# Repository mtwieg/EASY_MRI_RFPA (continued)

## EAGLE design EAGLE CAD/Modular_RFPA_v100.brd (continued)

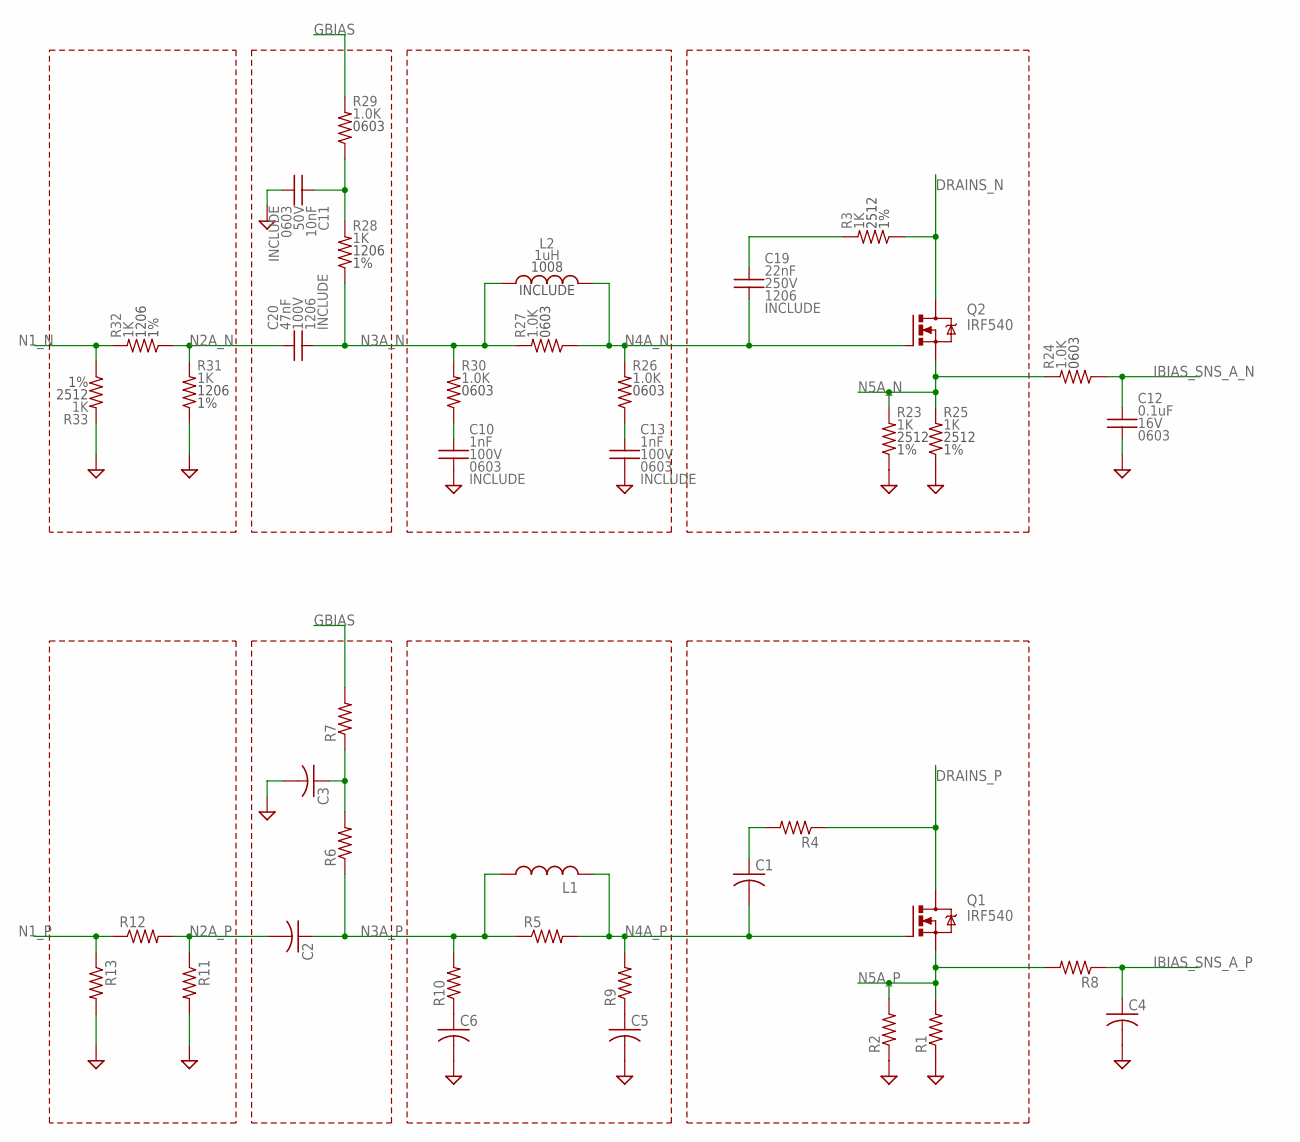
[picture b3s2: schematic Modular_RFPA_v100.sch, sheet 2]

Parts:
C1: C-USC1812; C1812
C2: C-USC0805; C0805
C3, C4, C5, C6: C-USC0603; C0603
C10, C13: 1nF; 0603_IPC-7351B
C11: 10nF; 0603_IPC-7351B
C12: 0.1uF; 0603_IPC-7351B
C19: 22nF; C1206
C20: 47nF; C1206
L1: L-USL1812; L1812
L2: 1uH; L1008
Q1, Q2: IRF540; TO220BV
R1, R2, R4, R11, R12, R13: R-US_R2512; R2512
R3, R23, R25, R33: 1K; R2512
R5, R6, R9, R10: R-US_R0805; R0805
R7, R8: R-US_R0603; R0603
R24, R26, R27, R29, R30: 1.0K; 0603_IPC-7351B
R28, R31, R32: 1K; R1206

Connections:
DRAINS_N: Q2.D, R3.2
DRAINS_P: Q1.D, R4.1
GBIAS: R7.2, R29.1; also elsewhere on the board
GND: C3.2, C4.2, C5.2, C6.2, C10.2, C11.2, C12.2, C13.2, R1.1, R2.1, R11.2, R13.2, R23.2, R25.2, R31.2, R33.1; also elsewhere on the board
IBIAS_SNS_A_N: C12.1, R24.2
IBIAS_SNS_A_P: C4.1, R8.1
N1_N: R32.1, R33.2
N1_P: R12.1, R13.1
N2A_N: C20.1, R31.1, R32.2
N2A_P: C2.2, R11.1, R12.2
N3A_N: C20.2, L2.1, R27.1, R28.2, R30.1
N3A_P: C2.1, L1.1, R5.1, R6.1, R10.2
N4A_N: C19.2, L2.2, Q2.G, R26.1, R27.2
N4A_P: C1.2, L1.2, Q1.G, R5.2, R9.2
N5A_N: Q2.S, R23.1, R24.1, R25.1
N5A_P: Q1.S, R1.2, R2.2, R8.2
unnamed: C1.1, R4.2
unnamed: C10.1, R30.2
unnamed: C3.1, R6.2, R7.1
unnamed: C19.1, R3.1
unnamed: C5.1, R9.1
unnamed: C6.1, R10.1
unnamed: C11.1, R28.1, R29.2
unnamed: C13.1, R26.2

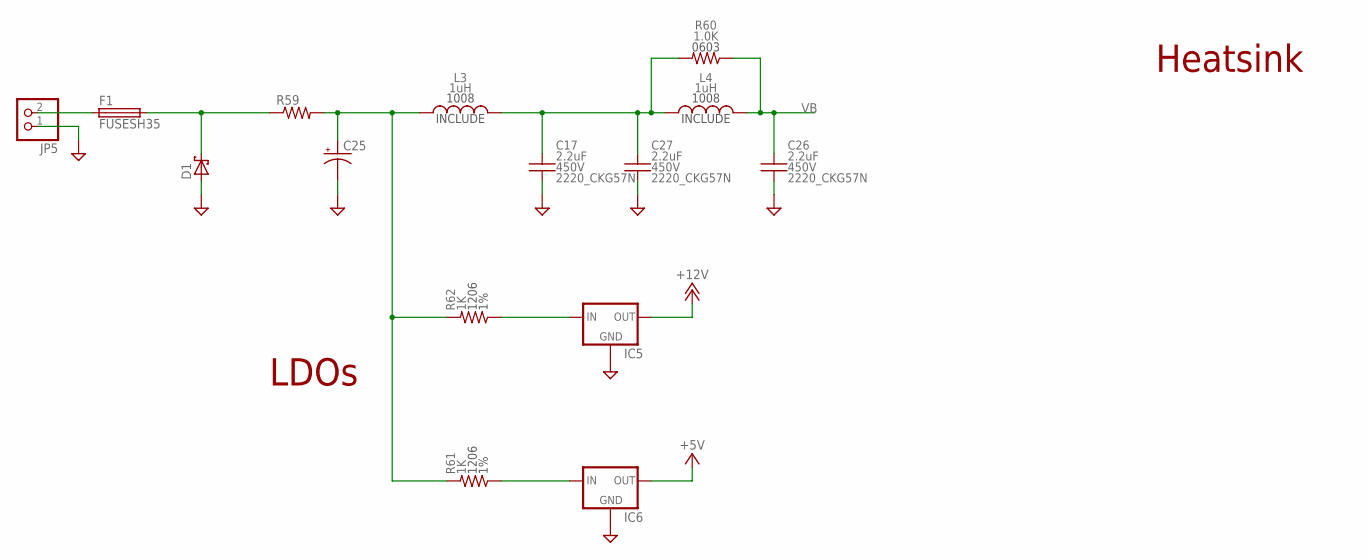
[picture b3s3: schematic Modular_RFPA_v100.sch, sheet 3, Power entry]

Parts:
C17, C26, C27: 2.2uF; C2220_CKG57N
C25: CPOL-USE10-25; EB25D
D1: SCHOTTKY-DIODESMC; SMC
F1: FUSESH35; SH25
IC5, IC6: 78XXS
JP5: PINHD-1X2; 1X02
L3, L4: 1uH; L1008
R59: R-US_0617/22; 0617/22
R60: 1.0K; 0603_IPC-7351B
R61, R62: 1K; R1206

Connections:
+5V: IC6.OUT
+12V: IC5.OUT; also elsewhere on the board
GND: C17.2, C25.-, C26.2, C27.2, D1.A, IC5.GND, IC6.GND, JP5.1; also elsewhere on the board
unnamed: IC5.IN, R62.2
unnamed: D1.C, F1.2, R59.1
unnamed: F1.1, JP5.2
unnamed: C25.+, L3.1, R59.2, R61.1, R62.1
unnamed: C17.1, C27.1, L3.2, L4.1, R60.1
unnamed: IC6.IN, R61.2
VB: C26.1, L4.2, R60.2

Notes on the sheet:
LDOs
Heatsink

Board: 4 copper layers, 100 parts (0 on the bottom side), 60 nets, no tracks yet.

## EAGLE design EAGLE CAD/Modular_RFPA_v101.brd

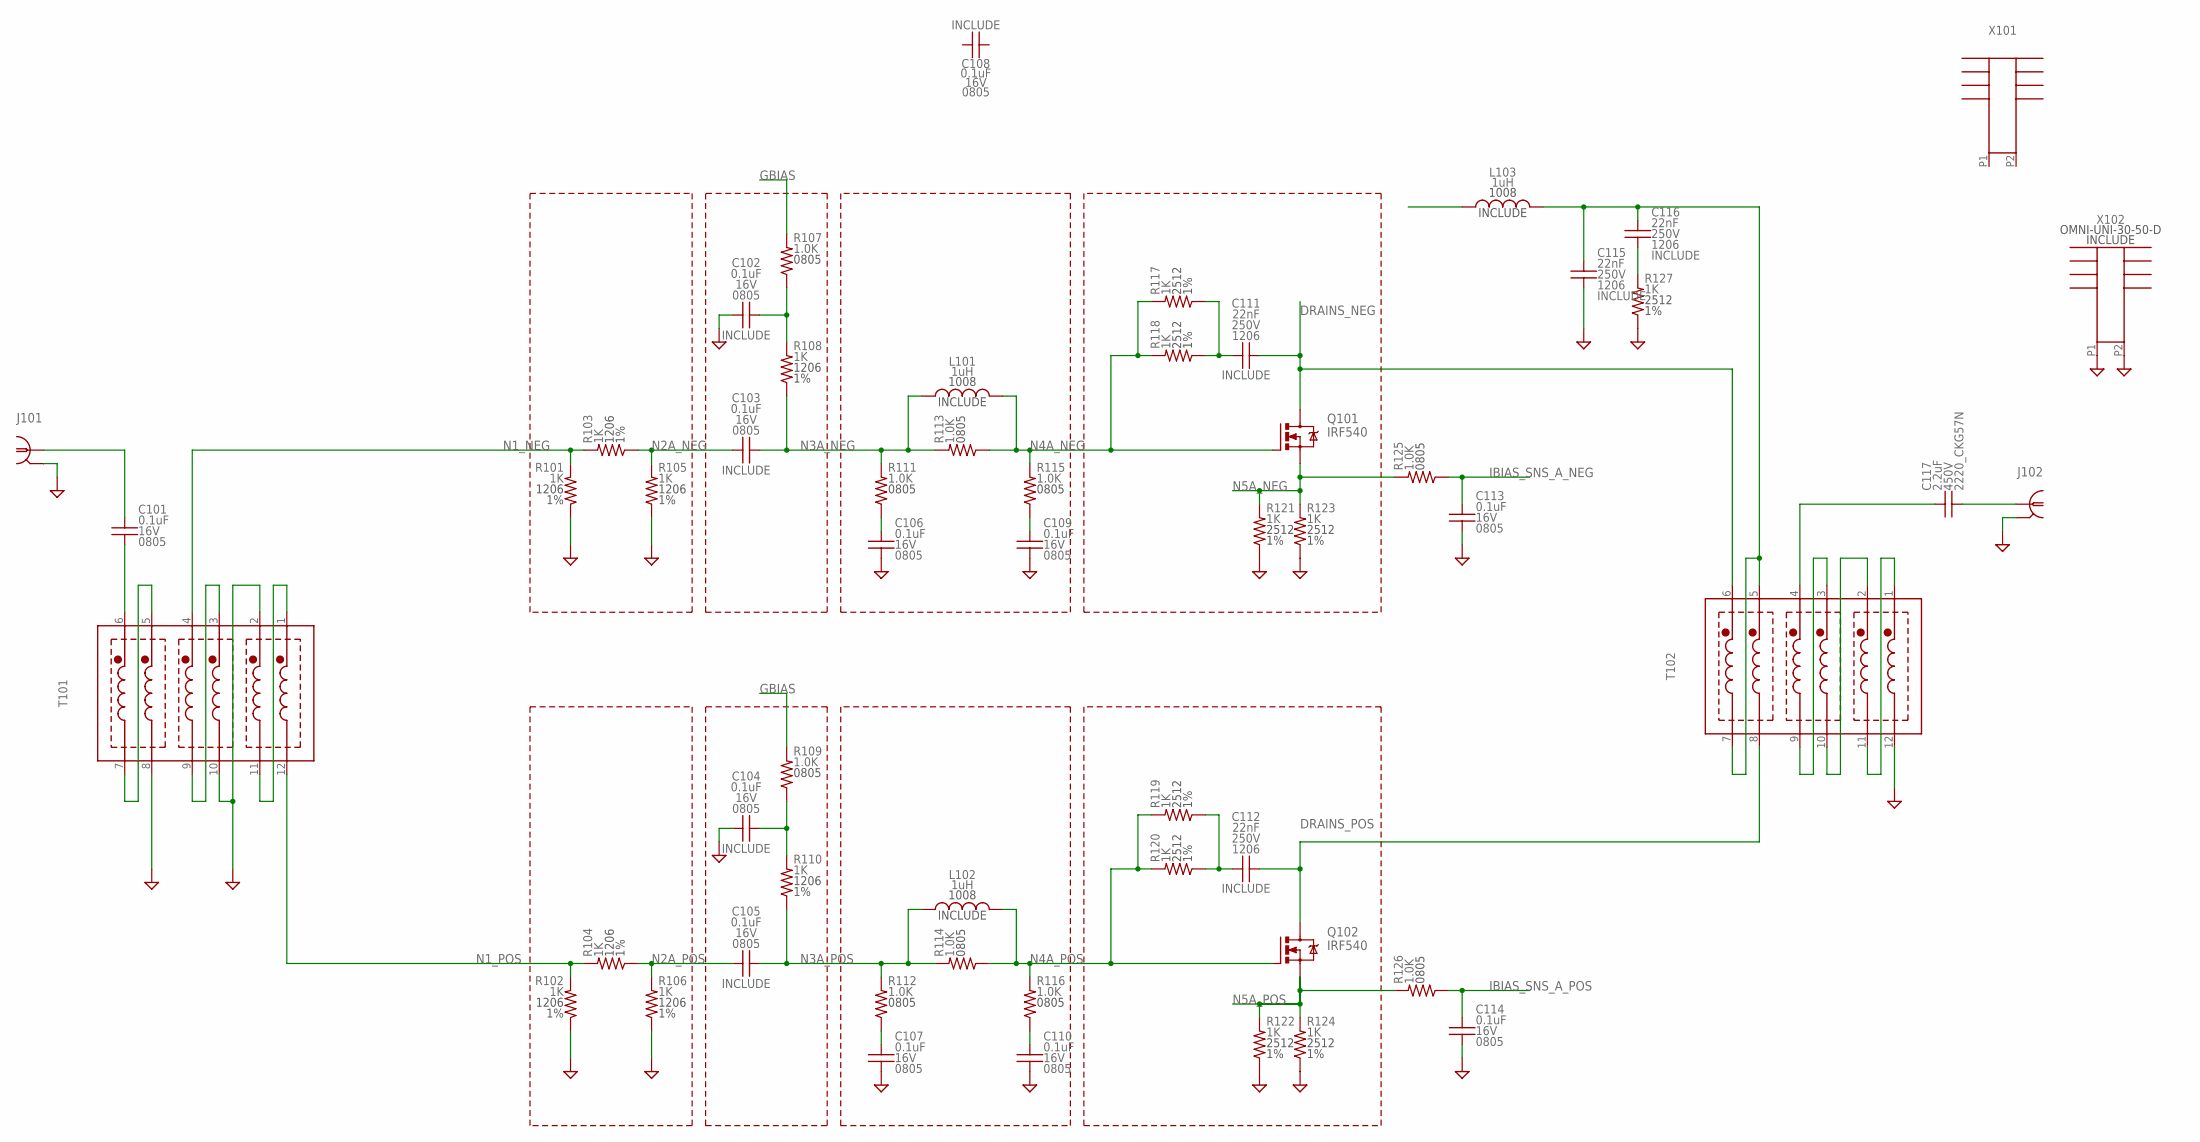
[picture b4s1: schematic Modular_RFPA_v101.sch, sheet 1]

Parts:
C101, C102, C103, C104, C105, C106, C107, C108, C109, C110, C113, C114: 0.1uF; 0805_IPC-7351B
C111, C112, C115, C116: 22nF; C1206
C117: 2.2uF; C2220_CKG57N
J101, J102: COAXBNC_EDGE; BNC_EDGE
L101, L102, L103: 1uH; L1008
Q101, Q102: IRF540; TO220BV
R101, R102, R103, R104, R105, R106, R108, R110: 1K; R1206
R107, R109, R111, R112, R113, R114, R115, R116, R125, R126: 1.0K; 0805_IPC-7351B
R117, R118, R119, R120, R121, R122, R123, R124, R127: 1K; R2512
T101, T102: HP5_TRAFOHP5; HP5
X101: HEATSINK_OMNI_DUAL30-75-D; OMNI-UNI-30-75-D
X102: HEATSINK_OMNI_DUALOMNI-UNI-30-50-DUNI-30-50-D; OMNI-UNI-30-50-D

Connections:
DRAINS_NEG: C111.2, Q101.D, T102.6 (S6)
DRAINS_POS: C112.2, Q102.D, T102.8 (F5)
GBIAS: R107.1, R109.1; also elsewhere on the board
GND: C102.2, C104.2, C106.2, C107.2, C109.2, C110.2, C113.2, C114.2, C115.2, J101.G1 (GND1), J101.G2 (GND1), J101.G3 (GND1), J101.G4 (GND1), J102.G1 (GND1), J102.G2 (GND1), J102.G3 (GND1), J102.G4 (GND1), R101.2, R102.2, R105.2, R106.2, R121.2, R122.2, R123.2, R124.2, R127.2, T101.2 (S2), T101.8 (F5), T101.10 (F3), T102.12 (F1), X102.P1, X102.P2; also elsewhere on the board
IBIAS_SNS_A_NEG: C113.1, R125.2
IBIAS_SNS_A_POS: C114.1, R126.2
N1_NEG: R101.1, R103.1, T101.4 (S4)
N1_POS: R102.1, R104.1, T101.12 (F1)
N2A_NEG: C103.2, R103.2, R105.1
N2A_POS: C105.2, R104.2, R106.1
N3A_NEG: C103.1, L101.1, R108.2, R111.1, R113.1
N3A_POS: C105.1, L102.1, R110.2, R112.1, R114.1
N4A_NEG: L101.2, Q101.G, R113.2, R115.1, R117.1, R118.1
N4A_POS: L102.2, Q102.G, R114.2, R116.1, R119.1, R120.1
N5A_NEG: Q101.S, R121.1, R123.1, R125.1
N5A_POS: Q102.S, R122.1, R124.1, R126.1
unnamed: C111.1, R117.2, R118.2
unnamed: C106.1, R111.2
unnamed: C104.1, R109.2, R110.1
unnamed: C107.1, R112.2
unnamed: C110.1, R116.2
unnamed: C112.1, R119.2, R120.2
unnamed: C102.1, R107.2, R108.1
unnamed: C109.1, R115.2
unnamed: T102.3 (S3), T102.9 (F4)
unnamed: T102.2 (S2), T102.10 (F3)
unnamed: T102.1 (S1), T102.11 (F2)
unnamed: T101.3 (S3), T101.9 (F4)
unnamed: C117.2, J102.C (1)
unnamed: C117.1, T102.4 (S4)
unnamed: T101.1 (S1), T101.11 (F2)
unnamed: C101.1, J101.C (1)
unnamed: C116.2, R127.1
unnamed: C101.2, T101.6 (S6)
VB_CT: C115.1, C116.1, L103.2, T102.5 (S5), T102.7 (F6)
VB_CT1: T101.5 (S5), T101.7 (F6)

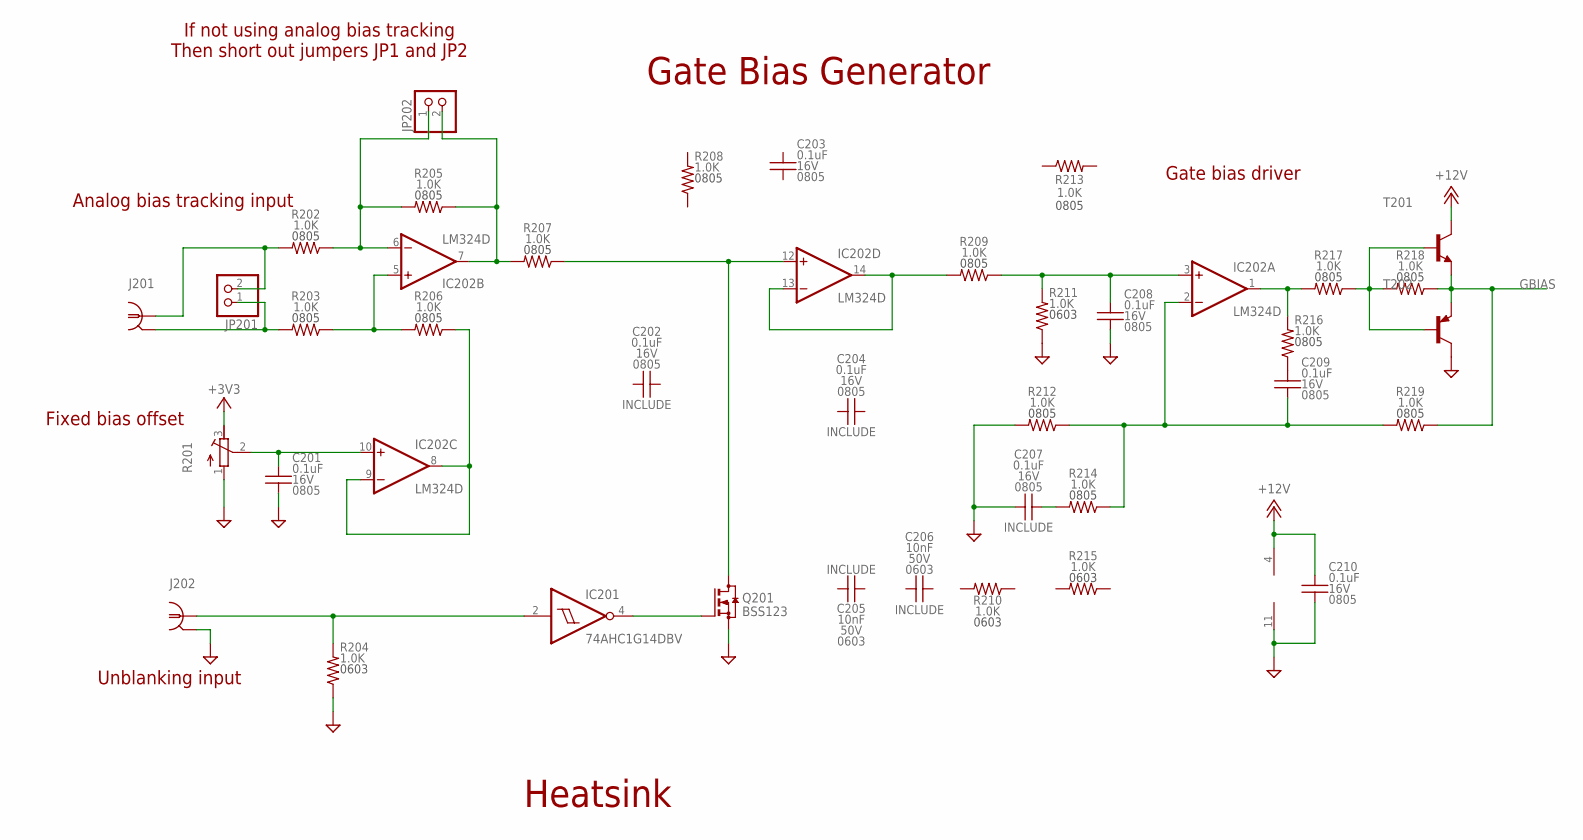
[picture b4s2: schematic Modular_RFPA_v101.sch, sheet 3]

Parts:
C201, C202, C203, C204, C207, C208, C209, C210: 0.1uF; 0805_IPC-7351B
C205, C206: 10nF; 0603_IPC-7351B
IC201: 74AHC1G14DBV; SOT23-5
IC202: LM324D; SO14
J201, J202: COAXBNC_EDGE; BNC_EDGE
JP201, JP202: PINHD-1X2; 1X02
Q201: BSS123; SOT23
R201: R-TRIMM3299W; RTRIM3299W
R202, R203, R205, R206, R207, R208, R209, R212, R213, R214, R216, R217, R218, R219: 1.0K; 0805_IPC-7351B
R204, R210, R211, R215: 1.0K; 0603_IPC-7351B
T201: BC808-NPN-SOT23-BEC; SOT23-BEC
T202: BC807-16-PNP-SOT23-BEC; SOT23-BEC

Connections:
+3V3: R201.3 (E)
+12V: C210.1, IC202.4 (V+), T201.C; also elsewhere on the board
GBIAS: R218.2, R219.2, T201.E, T202.E; also elsewhere on the board
GND: C201.2, C207.2, C208.2, C210.2, IC201.3 (GND), IC202.11 (V-), J202.G1 (GND1), J202.G2 (GND1), J202.G3 (GND1), J202.G4 (GND1), Q201.2 (S), R201.1 (A), R204.2, R211.2, R212.1, T202.C; also elsewhere on the board
unnamed: IC202.1 (OUT), R216.1, R217.1
unnamed: R217.2, R218.1, T201.B, T202.B
unnamed: IC201.2 (I), J202.C (1), R204.1
unnamed: IC202.13 (-IN), IC202.14 (OUT), R209.1
unnamed: C209.1, R216.2
unnamed: C207.1, R214.1
unnamed: C209.2, IC202.2 (-IN), R212.2, R214.2, R219.1
unnamed: C208.1, IC202.3 (+IN), R209.2, R211.1
unnamed: IC202.5 (+IN), R203.2, R206.1
unnamed: IC202.7 (OUT), JP202.2, R205.2, R207.1
unnamed: IC202.6 (-IN), JP202.1, R202.2, R205.1
unnamed: J201.C (1), JP201.2, R202.1
unnamed: J201.G1 (GND1), J201.G2 (GND1), J201.G3 (GND1), J201.G4 (GND1), JP201.1, R203.1
unnamed: IC202.12 (+IN), Q201.3 (D), R207.2
unnamed: IC201.4 (O), Q201.1 (G)
unnamed: C201.1, IC202.10 (+IN), R201.2 (S)
unnamed: IC202.8 (OUT), IC202.9 (-IN), R206.2
VCC: IC201.5 (VCC)

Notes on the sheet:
Gate Bias Generator
Heatsink
If not using analog bias tracking Then short out jumpers JP1 and JP2
Analog bias tracking input
Fixed bias offset
Gate bias driver
Unblanking input

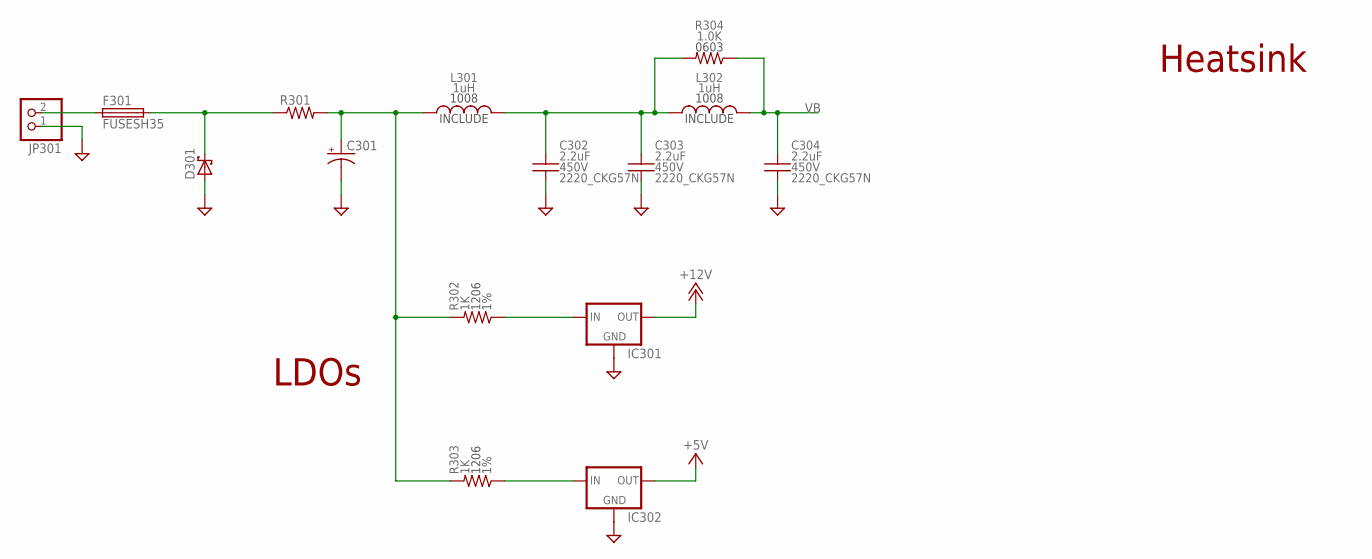
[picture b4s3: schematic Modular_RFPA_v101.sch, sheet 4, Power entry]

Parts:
C301: CPOL-USE10-25; EB25D
C302, C303, C304: 2.2uF; C2220_CKG57N
D301: SCHOTTKY-DIODESMC; SMC
F301: FUSESH35; SH25
IC301, IC302: 78XXS
JP301: PINHD-1X2; 1X02
L301, L302: 1uH; L1008
R301: R-US_0617/22; 0617/22
R302, R303: 1K; R1206
R304: 1.0K; 0603_IPC-7351B

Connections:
+5V: IC302.OUT
+12V: IC301.OUT; also elsewhere on the board
GND: C301.-, C302.2, C303.2, C304.2, D301.A, IC301.GND, IC302.GND, JP301.1; also elsewhere on the board
unnamed: IC301.IN, R302.2
unnamed: D301.C, F301.2, R301.1
unnamed: F301.1, JP301.2
unnamed: C301.+, L301.1, R301.2, R302.1, R303.1
unnamed: C302.1, C303.1, L301.2, L302.1, R304.1
unnamed: IC302.IN, R303.2
VB: C304.1, L302.2, R304.2

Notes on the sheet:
LDOs
Heatsink

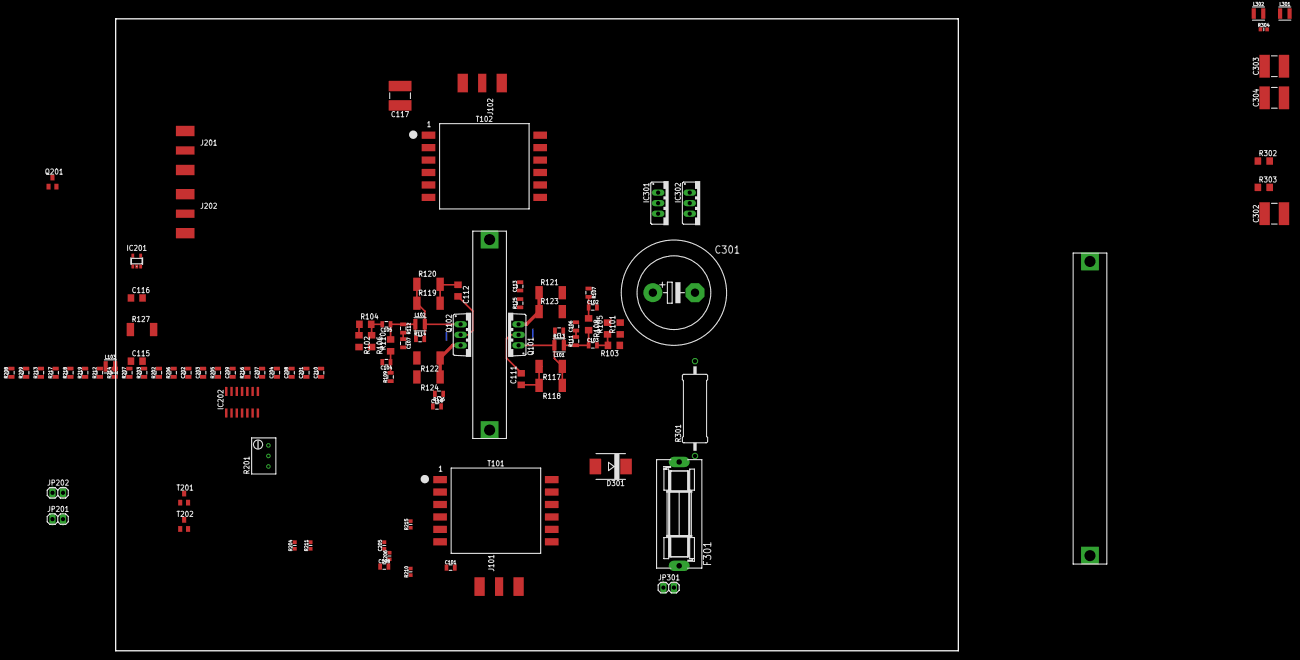
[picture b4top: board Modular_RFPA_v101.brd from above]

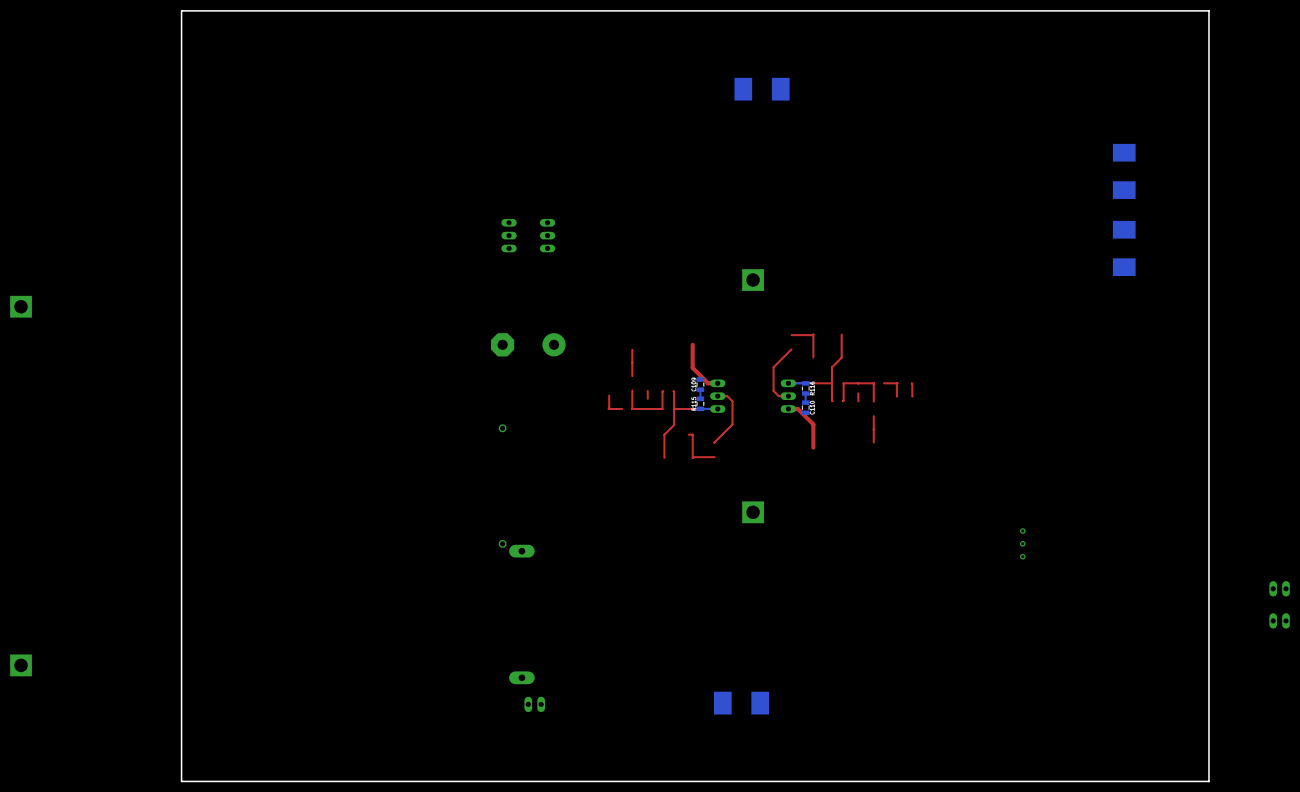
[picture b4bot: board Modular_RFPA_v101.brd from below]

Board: 4 copper layers, 203.2 x 152.4 mm, 108 parts (4 on the bottom side), 61 nets.
